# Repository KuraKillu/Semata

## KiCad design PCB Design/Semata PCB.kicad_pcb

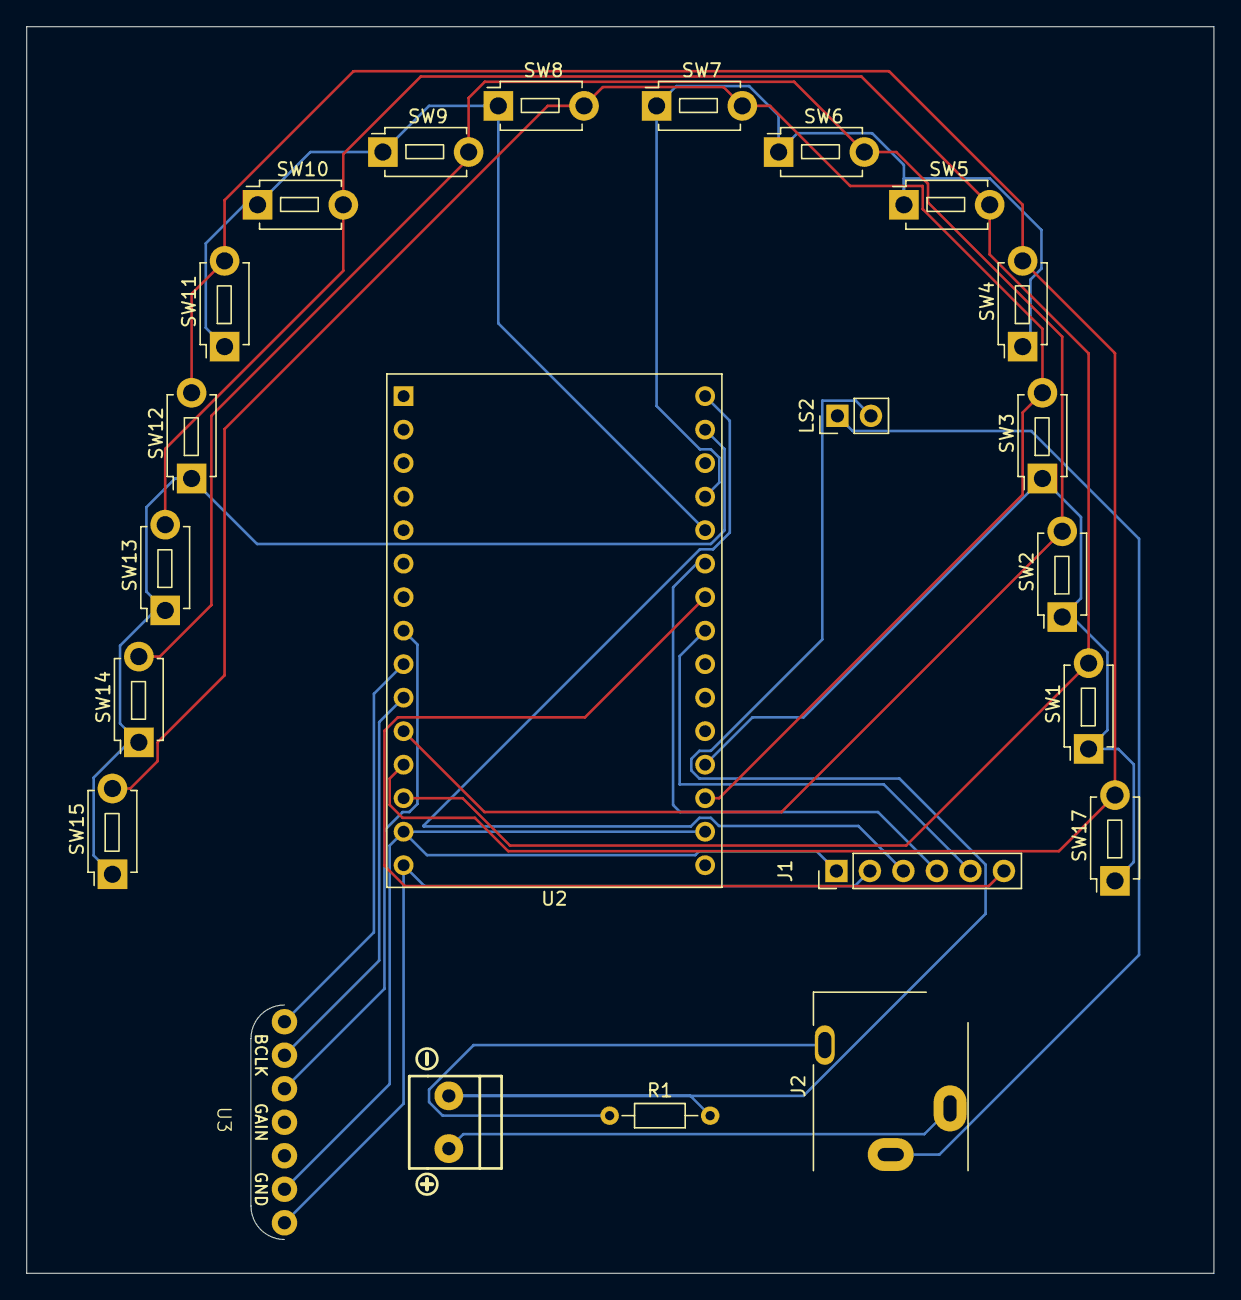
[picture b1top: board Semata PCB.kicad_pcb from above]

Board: 2 copper layers, 90.0 x 94.5 mm, 22 parts (0 on the bottom side), 21 nets.

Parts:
J1: Micro_SD_Card_Det1; PinHeader_1x06_P2.54mm_Vertical
J2: AudioJack2_Ground; Jack_3.5mm_CUI_SJ1-3513N_Horizontal
LS2: Speaker; PinHeader_1x02_P2.54mm_Vertical
R1: R; R_Axial_DIN0204_L3.6mm_D1.6mm_P7.62mm_Horizontal
SW1, SW2, SW3, SW4, SW5, SW6, SW7, SW8, SW9, SW10, SW11, SW12, SW13, SW14, SW15, SW17: SW_Push; SW_PUSH_1P1T_6x3.5mm_H4.3_APEM_MJTP1243
U2: ESP32-WROOM-32; ESP32-C3-DevKitM-1
U3: MAX98357A; MAX98357

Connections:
unnamed: J1.5 (CLK), U2.30 (IO18)
unnamed: J1.3 (CMD), U2.37 (IO23)
unnamed: J1.7 (DAT0), U2.31 (IO19)
unnamed: J1.2 (DAT3/CD), U2.29 (IO5)
unnamed: J1.4 (VDD), U2.2 (VDD), U3.7 (VDD)
unnamed: J1.6 (VSS), U2.1 (GND), U3.3 (GND)
unnamed: J2.G, R1.1
unnamed: J2.S, LS2.1
unnamed: SW1.1, SW2.1, SW3.1, SW17.1, U2.24 (IO2)
unnamed: SW4.2, SW11.2, SW12.2, SW17.2, U2.14 (IO12)
unnamed: SW1.2, SW5.2, SW10.2, SW13.2, U2.16 (IO13)
unnamed: SW2.2, SW6.2, SW9.2, SW14.2, U2.13 (IO14)
unnamed: SW3.2, SW7.2, SW8.2, SW15.2, U2.23 (IO15)
unnamed: SW8.1, SW9.1, SW10.1, SW11.1, U2.33 (IO21)
unnamed: SW12.1, SW13.1, SW14.1, SW15.1, U2.36 (IO22)
unnamed: U2.10 (IO25), U3.1 (DIN)
unnamed: U2.11 (IO26), U3.14 (LRCLK)
unnamed: U2.12 (IO27), U3.16 (BCLK)
unnamed: SW4.1, SW5.1, SW6.1, SW7.1, U2.34 (RXD0/IO3)
unnamed: LS2.2, R1.2, U3.10 (OUTN)
unnamed: J2.T, U3.9 (OUTP)

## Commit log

2025-06-29 adding semata to github
